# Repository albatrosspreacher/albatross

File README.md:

# Albatross

The Albatross is a modified version of the Alice layout. This is a split-fixed, 62-key, staggered keyboard. The current version does **not** have - hotswap, backlight (of any kind), and wireless capabilities.

## Layout

## Process

### PCB Design

This was my first time designing a PCB! I made a 2-layer PCB with rows routed in the front layer and columns in the back layer. This keyboard uses the Elite-C microcontroller.

### Keymap

#### Layer 1

#### Layer 2

### Wiring

### Schematic

### Aesthetic Choices

The Albatross is a unique bird. One of its skills, called dynamic soaring, is a zero-energy flight technique, which seems nothing short of intuitive to the naive tubenose; it allows the bird to fly thousands of miles without flapping its wings. Like the Albatross, we rely on intuition while doing our chores or completing any simple or complex daily task. With technology at the forefront of almost every industry, we rely on computers for assistance with our chores. Technology and its applications are seen as carefully crafted experiences incorporating human psychology with design principles in a little package delivered to us as a product. As a technologist, one of my primary goals is to make information systems accessible and usable for everyone. Keeping up with this mission, I designed this modified version of the Alice layout — the Albatross.

The cut at the bottom of the case and PCB has an upward arrow highlighting the albatross’s soaring techniques. The case is made from a clear 1.5mm acrylic sheet — staying true to the idea of transparency and usability — the case is see-through, and everyone can see the inner workings of the board easily. The botanical keycaps represent flora; paired with the albatross outline on the silkscreen of the PCB, which represents fauna, we get a 360 picture of nature. The switches are silent and linear; the keyboard allows you to immerse yourself in the sounds of your surroundings without the distraction of clattering keys.

### Acknowledgements

This keyboard's assembly and PCB design would have been impossible without the support and help of many folks, especially Joey Castillo. Huge shoutout – thanks, Joey!

### Future Work
Using a thin material like 1.5mm acrylic for the keyboard proved beneficial for aesthetics and acoustics but required careful handling due to its fragility, as a small crack occurred during assembly. Planned improvements for the next iteration include adjusting the spacing between the “>” and “:” keys for better usability, adding a silkscreen design to the top layer for enhanced aesthetics, and designing a cover with an integrated wrist rest for improved ergonomics. Additionally, since this is a sensory-friendly board, creating a cover to hide the bright blue light from the Elite-C microcontroller is a priority. Exploring a switch to a BLE-supported microcontroller paired with a long-lasting battery is also under consideration. Further plans involve testing more variations of ergonomic layouts and experimenting with different case angles to optimize comfort and functionality.

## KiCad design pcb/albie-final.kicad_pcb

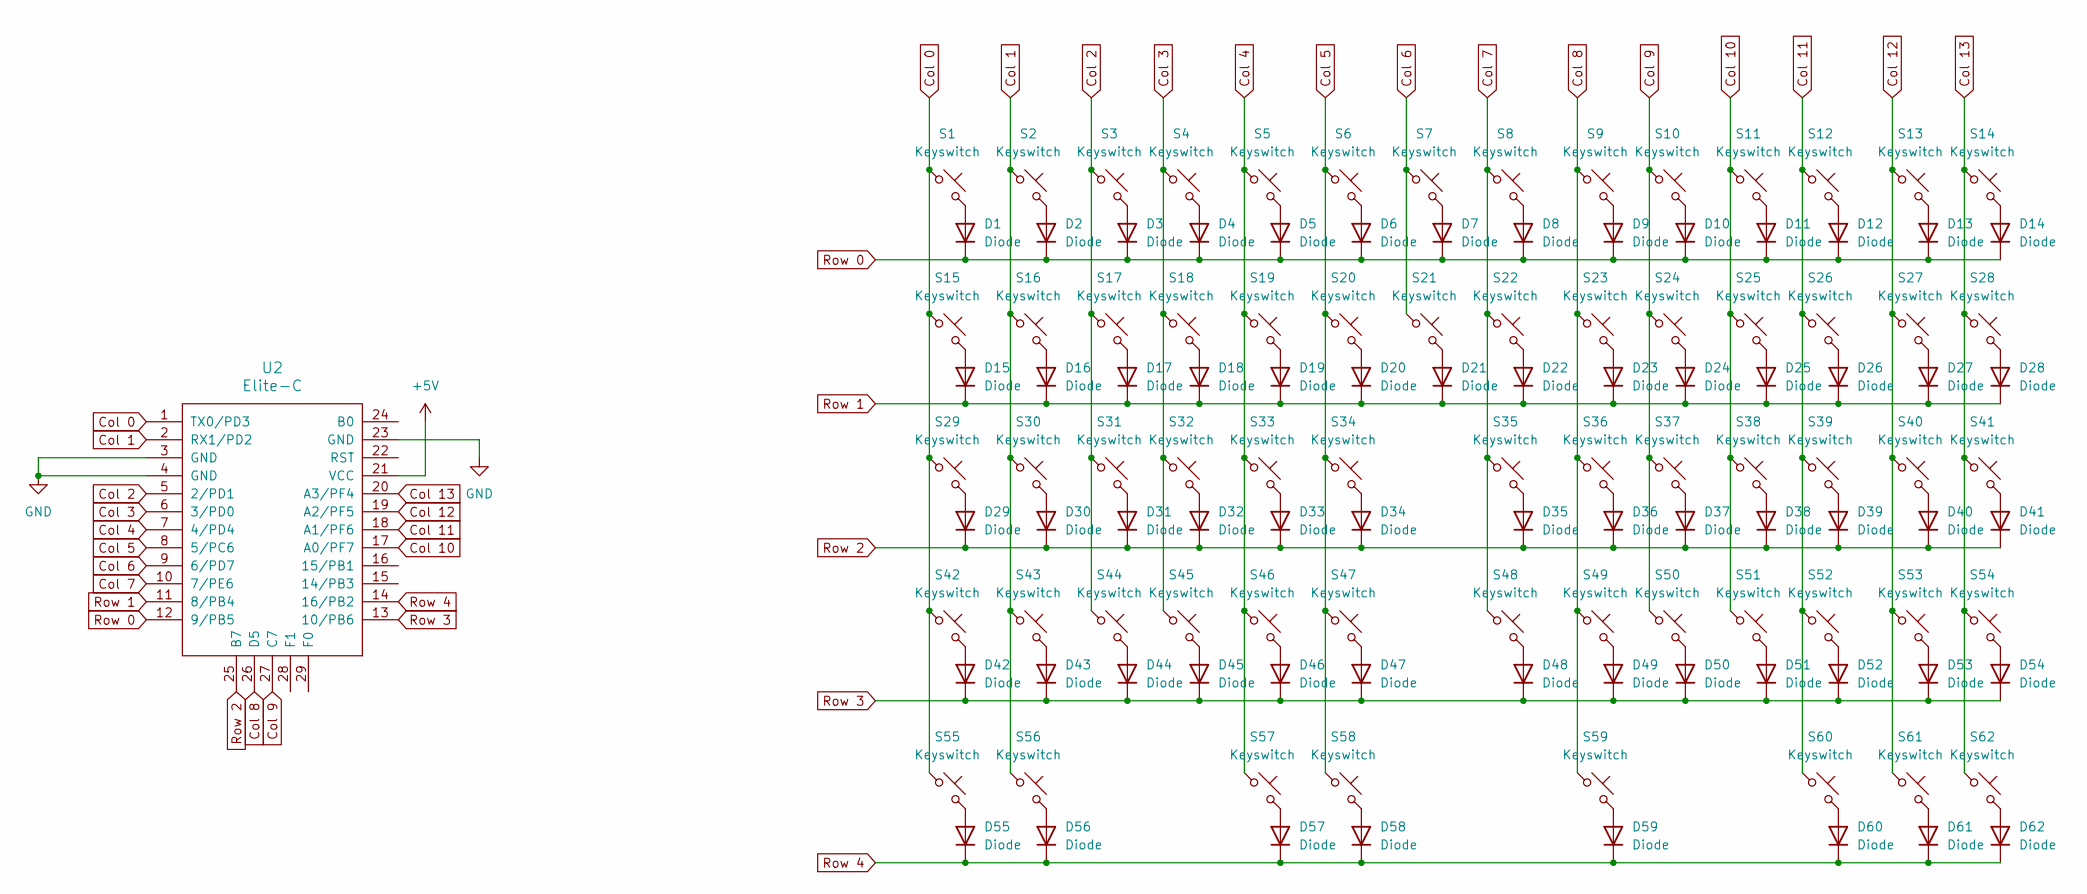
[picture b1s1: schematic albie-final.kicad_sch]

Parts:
D1, D2, D3, D4, D5, D6, D7, D8, D9, D10, D11, D12, D13, D14, D15, D16, D17, D18, D19, D20, D21, D22, D23, D24, D25, D26, D27, D28, D29, D30, D31, D32, D33, D34, D35, D36, D37, D38, D39, D40, D41, D42, D43, D44, D45, D46, D47, D48, D49, D50, D51, D52, D53, D54, D55, D56, D57, D58, D59, D60, D61, D62: Diode; Diode_DO-35
S1, S2, S3, S4, S5, S6, S7, S8, S9, S10, S11, S12, S13, S16, S17, S18, S19, S20, S21, S22, S23, S24, S25, S26, S27, S30, S31, S32, S33, S34, S35, S36, S37, S38, S39, S40, S43, S44, S45, S46, S47, S48, S49, S50, S51, S52, S53, S60: Keyswitch; MX_PCB_1.00u
S14: Keyswitch; MXOnly-2U
S15, S28, S55, S56, S61, S62: Keyswitch; MX_PCB_1.50u
S29: Keyswitch; MX_PCB_1.75u
S41, S42: Keyswitch; MXOnly-2.25U
S54, S57: Keyswitch; MXOnly-2.75U
S58: Keyswitch; MX_PCB_1.25u
S59: Keyswitch; MXOnly-3U
U2: Elite-C; Elite-C-castellated-29pin-holes

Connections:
+5V: U2.21 (VCC)
Col 0: S1.1, S15.1, S29.1, S42.1, S55.1, U2.1 (TX0/PD3)
Col 1: S2.1, S16.1, S30.1, S43.1, S56.1, U2.2 (RX1/PD2)
Col 2: S3.1, S17.1, S31.1, S44.1, U2.5 (2/PD1)
Col 3: S4.1, S18.1, S32.1, S45.1, U2.6 (3/PD0)
Col 4: S5.1, S19.1, S33.1, S46.1, S57.1, U2.7 (4/PD4)
Col 5: S6.1, S20.1, S34.1, S47.1, S58.1, U2.8 (5/PC6)
Col 6: S7.1, S21.1, U2.9 (6/PD7)
Col 7: S8.1, S22.1, S35.1, S48.1, U2.10 (7/PE6)
Col 8: S9.1, S23.1, S36.1, S49.1, S59.1, U2.26 (D5)
Col 9: S10.1, S24.1, S37.1, S50.1, U2.27 (C7)
Col 10: S11.1, S25.1, S38.1, S51.1, U2.17 (A0/PF7)
Col 11: S12.1, S26.1, S39.1, S52.1, S60.1, U2.18 (A1/PF6)
Col 12: S13.1, S27.1, S40.1, S53.1, S61.1, U2.19 (A2/PF5)
Col 13: S14.1, S28.1, S41.1, S54.1, S62.1, U2.20 (A3/PF4)
GND: U2.3 (GND), U2.4 (GND), U2.23 (GND)
unnamed: D1.2 (A), S1.2
unnamed: D2.2 (A), S2.2
unnamed: D3.2 (A), S3.2
unnamed: D4.2 (A), S4.2
unnamed: D5.2 (A), S5.2
unnamed: D6.2 (A), S6.2
unnamed: D7.2 (A), S7.2
unnamed: D8.2 (A), S8.2
unnamed: D9.2 (A), S9.2
unnamed: D10.2 (A), S10.2
unnamed: D11.2 (A), S11.2
unnamed: D12.2 (A), S12.2
unnamed: D13.2 (A), S13.2
unnamed: D14.2 (A), S14.2
unnamed: D15.2 (A), S15.2
unnamed: D16.2 (A), S16.2
unnamed: D17.2 (A), S17.2
unnamed: D18.2 (A), S18.2
unnamed: D19.2 (A), S19.2
unnamed: D20.2 (A), S20.2
unnamed: D21.2 (A), S21.2
unnamed: D22.2 (A), S22.2
unnamed: D23.2 (A), S23.2
unnamed: D24.2 (A), S24.2
unnamed: D25.2 (A), S25.2
unnamed: D26.2 (A), S26.2
unnamed: D27.2 (A), S27.2
unnamed: D28.2 (A), S28.2
unnamed: D29.2 (A), S29.2
unnamed: D30.2 (A), S30.2
unnamed: D31.2 (A), S31.2
unnamed: D32.2 (A), S32.2
unnamed: D33.2 (A), S33.2
unnamed: D34.2 (A), S34.2
unnamed: D35.2 (A), S35.2
unnamed: D36.2 (A), S36.2
unnamed: D37.2 (A), S37.2
unnamed: D38.2 (A), S38.2
unnamed: D39.2 (A), S39.2
unnamed: D40.2 (A), S40.2
unnamed: D41.2 (A), S41.2
unnamed: D42.2 (A), S42.2
unnamed: D43.2 (A), S43.2
unnamed: D44.2 (A), S44.2
unnamed: D45.2 (A), S45.2
unnamed: D46.2 (A), S46.2
unnamed: D47.2 (A), S47.2
unnamed: D48.2 (A), S48.2
unnamed: D49.2 (A), S49.2
unnamed: D50.2 (A), S50.2
unnamed: D51.2 (A), S51.2
unnamed: D52.2 (A), S52.2
unnamed: D53.2 (A), S53.2
unnamed: D54.2 (A), S54.2
unnamed: D55.2 (A), S55.2
unnamed: D56.2 (A), S56.2
unnamed: D57.2 (A), S57.2
unnamed: D58.2 (A), S58.2
unnamed: D59.2 (A), S59.2
unnamed: D60.2 (A), S60.2
unnamed: D61.2 (A), S61.2
unnamed: D62.2 (A), S62.2
Row 0: D1.1 (K), D2.1 (K), D3.1 (K), D4.1 (K), D5.1 (K), D6.1 (K), D7.1 (K), D8.1 (K), D9.1 (K), D10.1 (K), D11.1 (K), D12.1 (K), D13.1 (K), D14.1 (K), U2.12 (9/PB5)
Row 1: D15.1 (K), D16.1 (K), D17.1 (K), D18.1 (K), D19.1 (K), D20.1 (K), D21.1 (K), D22.1 (K), D23.1 (K), D24.1 (K), D25.1 (K), D26.1 (K), D27.1 (K), D28.1 (K), U2.11 (8/PB4)
Row 2: D29.1 (K), D30.1 (K), D31.1 (K), D32.1 (K), D33.1 (K), D34.1 (K), D35.1 (K), D36.1 (K), D37.1 (K), D38.1 (K), D39.1 (K), D40.1 (K), D41.1 (K), U2.25 (B7)
Row 3: D42.1 (K), D43.1 (K), D44.1 (K), D45.1 (K), D46.1 (K), D47.1 (K), D48.1 (K), D49.1 (K), D50.1 (K), D51.1 (K), D52.1 (K), D53.1 (K), D54.1 (K), U2.13 (10/PB6)
Row 4: D55.1 (K), D56.1 (K), D57.1 (K), D58.1 (K), D59.1 (K), D60.1 (K), D61.1 (K), D62.1 (K), U2.14 (16/PB2)

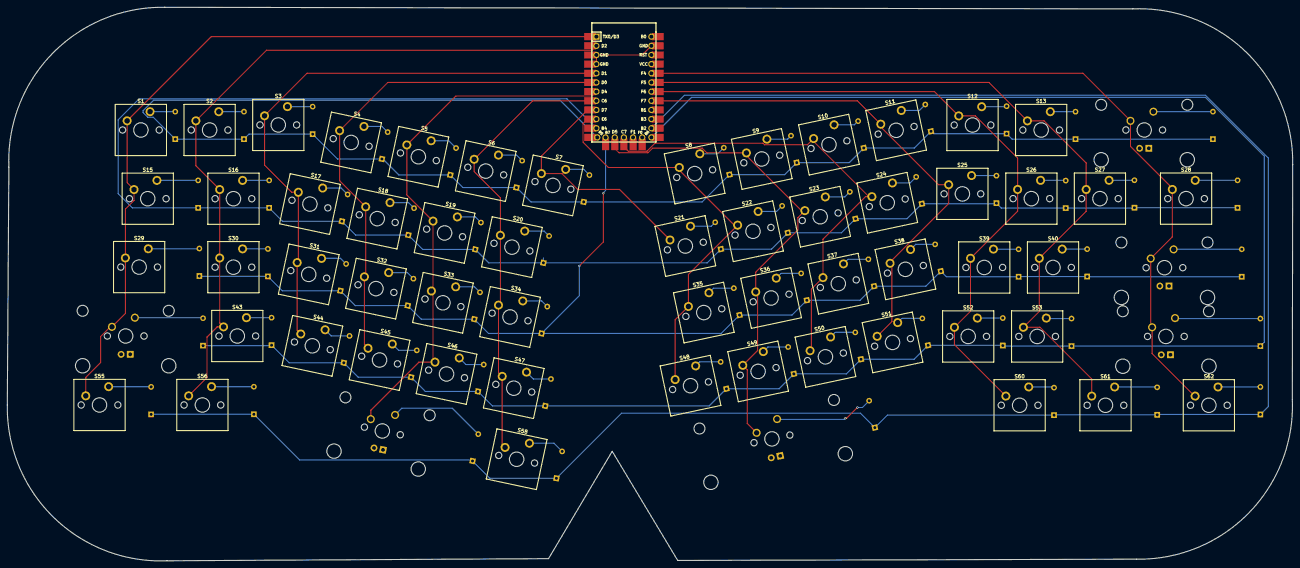
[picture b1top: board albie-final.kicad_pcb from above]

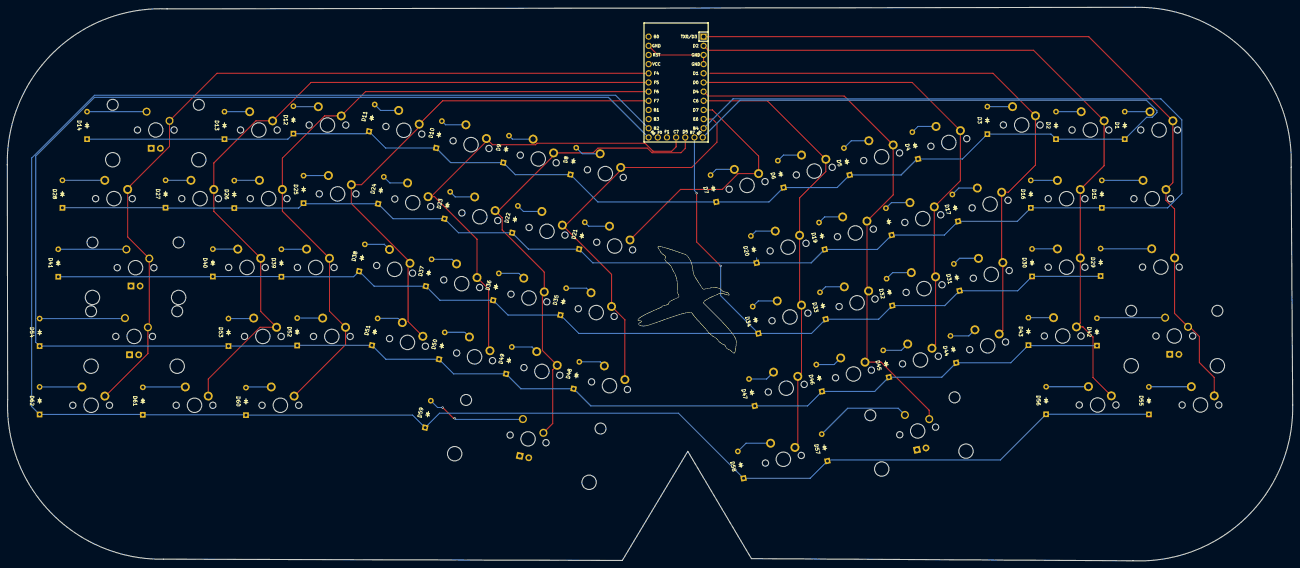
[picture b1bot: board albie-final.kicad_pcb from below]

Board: 2 copper layers, 356.3 x 153.5 mm, 126 parts (63 on the bottom side), 82 nets.

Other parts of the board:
Albatross: LOGO

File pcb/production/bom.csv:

Designator,Footprint,Quantity,Value,LCSC Part #
"D1, D10, D11, D12, D13, D14, D15, D16, D17, D18, D19, D2, D20, D21, D22, D23, D24, D25, D26, D27, D28, D29, D3, D30, D31, D32, D33, D34, D35, D36, D37, D38, D39, D4, D40, D41, D42, D43, D44, D45, D46, D47, D48, D49, D5, D50, D51, D52, D53, D54, D55, D56, D57, D58, D59, D6, D60, D61, D62, D7, D8, D9",Diode_DO-35,62,Diode,
"S1, S10, S11, S12, S13, S16, S17, S18, S19, S2, S20, S21, S22, S23, S24, S25, S26, S27, S3, S30, S31, S32, S33, S34, S35, S36, S37, S38, S39, S4, S40, S43, S44, S45, S46, S47, S48, S49, S5, S50, S51, S52, S53, S6, S60, S7, S8, S9",MX_PCB_1.00u,48,Keyswitch,
S14,MXOnly-2U,1,Keyswitch,
"S15, S28, S55, S56, S61, S62",MX_PCB_1.50u,6,Keyswitch,
S29,MX_PCB_1.75u,1,Keyswitch,
"S41, S42",MXOnly-2.25U,2,Keyswitch,
"S54, S57",MXOnly-2.75U,2,Keyswitch,
S58,MX_PCB_1.25u,1,Keyswitch,
S59,MXOnly-3U,1,Keyswitch,
U2,Elite-C-castellated-29pin-holes,1,Elite-C,

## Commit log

2024-12-10 all files! 🐦
2024-12-10 readme updated! :apple:
2024-12-10 adding final picture! 🍉
2024-12-10 final 🔻
